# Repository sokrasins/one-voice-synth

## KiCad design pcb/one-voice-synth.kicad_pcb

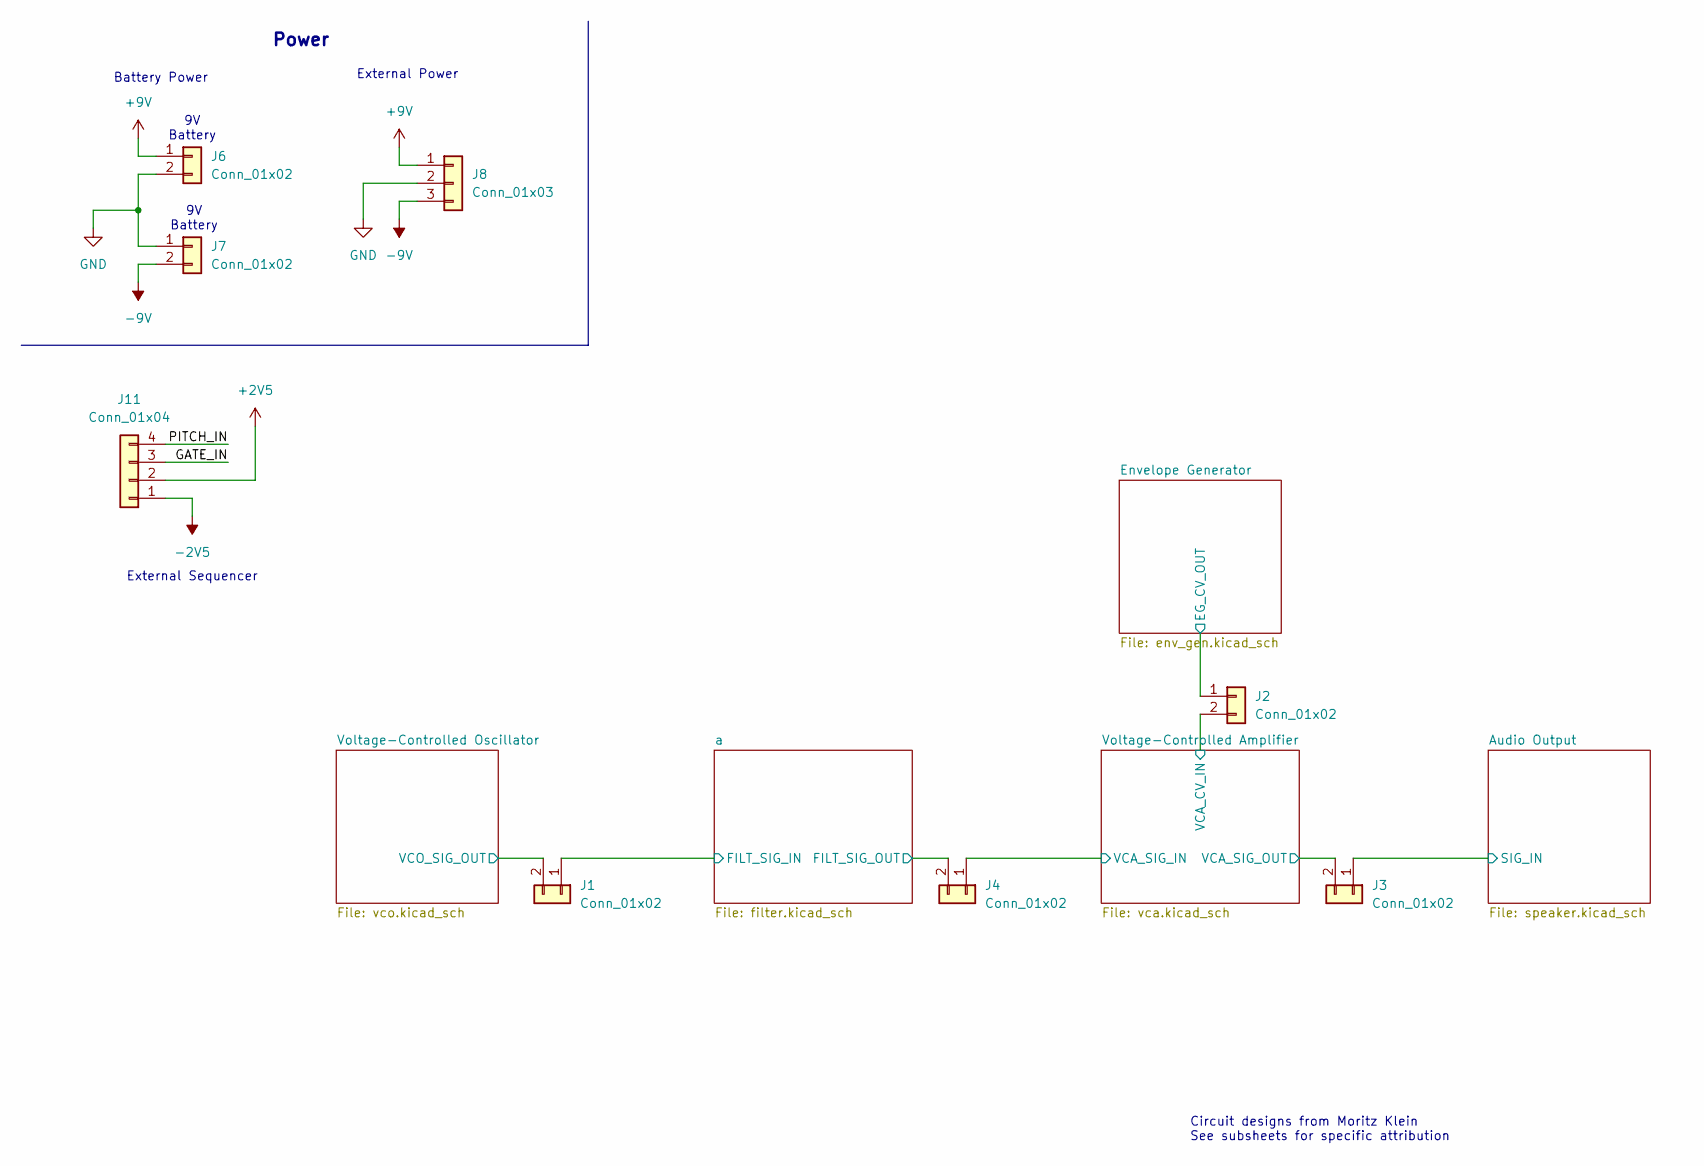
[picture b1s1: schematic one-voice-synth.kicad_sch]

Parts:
J1, J2, J3, J4, J6, J7: Conn_01x02; PinHeader_1x02_P2.54mm_Vertical
J8: Conn_01x03; PinHeader_1x03_P2.54mm_Horizontal
J11: Conn_01x04; PinHeader_1x04_P2.54mm_Vertical

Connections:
+2V5: J11.2; also elsewhere on the board
+9V: J6.1, J8.1; also elsewhere on the board
-2V5: J11.1; also elsewhere on the board
-9V: J7.2, J8.3; also elsewhere on the board
/Audio Output/SIG_IN: J3.1; also elsewhere on the board
/Envelope Generator/EG_CV_OUT: J2.1; also elsewhere on the board
/GATE_IN: J11.3
/PITCH_IN: J11.4
/Voltage-Controlled Amplifier/VCA_CV_IN: J2.2; also elsewhere on the board
/Voltage-Controlled Amplifier/VCA_SIG_IN: J4.1; also elsewhere on the board
/Voltage-Controlled Amplifier/VCA_SIG_OUT: J3.2; also elsewhere on the board
/Voltage-Controlled Oscillator/VCO_SIG_OUT: J1.2; also elsewhere on the board
/a/FILT_SIG_IN: J1.1; also elsewhere on the board
/a/FILT_SIG_OUT: J4.2; also elsewhere on the board
GND: J6.2, J7.1, J8.2; also elsewhere on the board

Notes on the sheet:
External Sequencer
Power
Circuit designs from Moritz Klein See subsheets for specific attribution
External Power
Battery Power
9V Battery

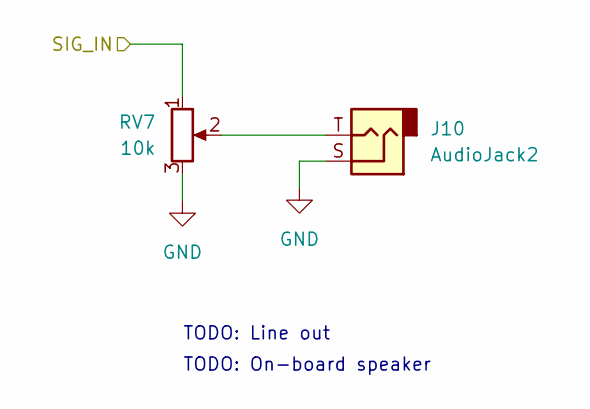
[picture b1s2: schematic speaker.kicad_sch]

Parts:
J10: AudioJack2; Jack_3.5mm_CUI_SJ1-3513N_Horizontal
RV7: 10k; Potentiometer_Bourns_PTV09A-1_Single_Vertical

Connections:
/Audio Output/SIG_IN: RV7.1; also elsewhere on the board
GND: J10.S, RV7.3; also elsewhere on the board
unnamed: J10.T, RV7.2

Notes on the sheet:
TODO: On-board speaker
TODO: Line out

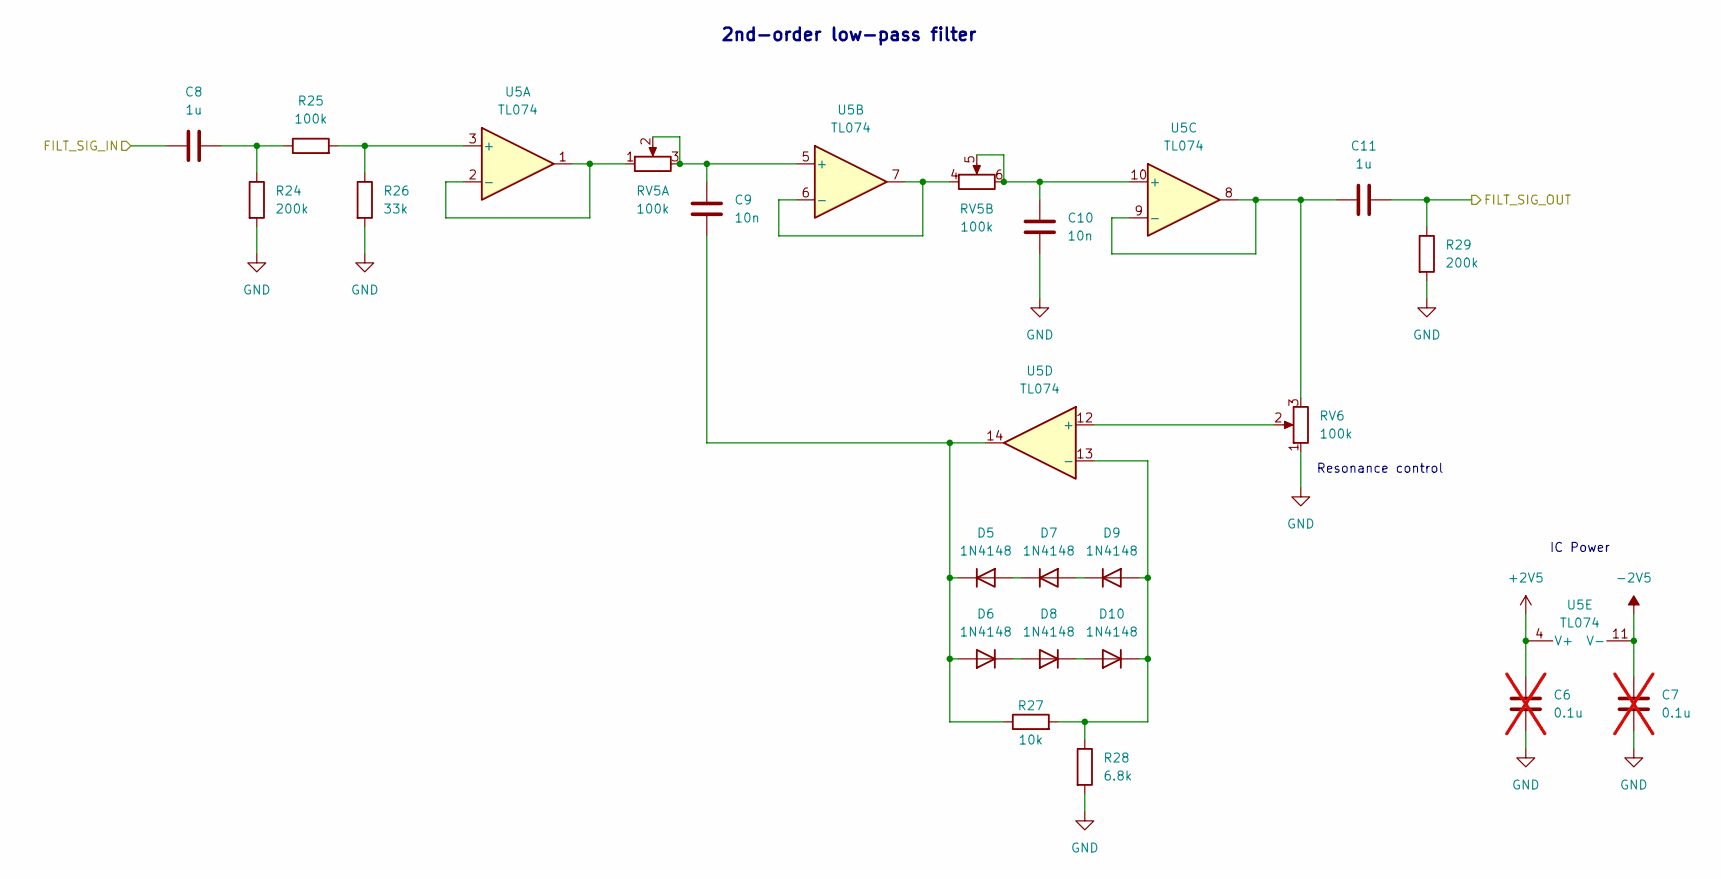
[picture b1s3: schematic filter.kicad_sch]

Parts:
C6, C7: 0.1u; C_Disc_D6.0mm_W2.5mm_P5.00mm; not fitted
C8, C11: 1u; C_Disc_D6.0mm_W2.5mm_P5.00mm
C9, C10: 10n; C_Disc_D6.0mm_W2.5mm_P5.00mm
D5, D6, D7, D8, D9, D10: 1N4148; D_DO-35_SOD27_P7.62mm_Horizontal
R24, R29: 200k; R_Axial_DIN0207_L6.3mm_D2.5mm_P10.16mm_Horizontal
R25: 100k; R_Axial_DIN0207_L6.3mm_D2.5mm_P10.16mm_Horizontal
R26: 33k; R_Axial_DIN0207_L6.3mm_D2.5mm_P10.16mm_Horizontal
R27: 10k; R_Axial_DIN0207_L6.3mm_D2.5mm_P10.16mm_Horizontal
R28: 6.8k; R_Axial_DIN0207_L6.3mm_D2.5mm_P10.16mm_Horizontal
RV5: 100k; Potentiometer_Bourns_PTV112-4_Dual_Vertical
RV6: 100k; Potentiometer_Bourns_PTV09A-1_Single_Vertical
U5: TL074; DIP-14_W7.62mm

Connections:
+2V5: C6.1, U5.4 (V+); also elsewhere on the board
-2V5: C7.1, U5.11 (V-); also elsewhere on the board
/a/FILT_SIG_IN: C8.1; also elsewhere on the board
/a/FILT_SIG_OUT: C11.2, R29.1; also elsewhere on the board
GND: C6.2, C7.2, C10.2, R24.2, R26.2, R28.2, R29.2, RV6.1; also elsewhere on the board
unnamed: C8.2, R24.1, R25.1
unnamed: D5.2 (A), D7.1 (K)
unnamed: C9.2, D5.1 (K), D6.2 (A), R27.1, U5.14
unnamed: D6.1 (K), D8.2 (A)
unnamed: D7.2 (A), D9.1 (K)
unnamed: D8.1 (K), D10.2 (A)
unnamed: D9.2 (A), D10.1 (K), R27.2, R28.1, U5.13 (-)
unnamed: R25.2, R26.1, U5.3 (+)
unnamed: RV5.1, U5.1, U5.2 (-)
unnamed: C9.1, RV5.2, RV5.3, U5.5 (+)
unnamed: RV5.4, U5.6 (-), U5.7
unnamed: C10.1, RV5.5, RV5.6, U5.10 (+)
unnamed: C11.1, RV6.3, U5.8, U5.9 (-)
unnamed: RV6.2, U5.12 (+)

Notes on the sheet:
IC Power
Resonance control
2nd-order low-pass filter

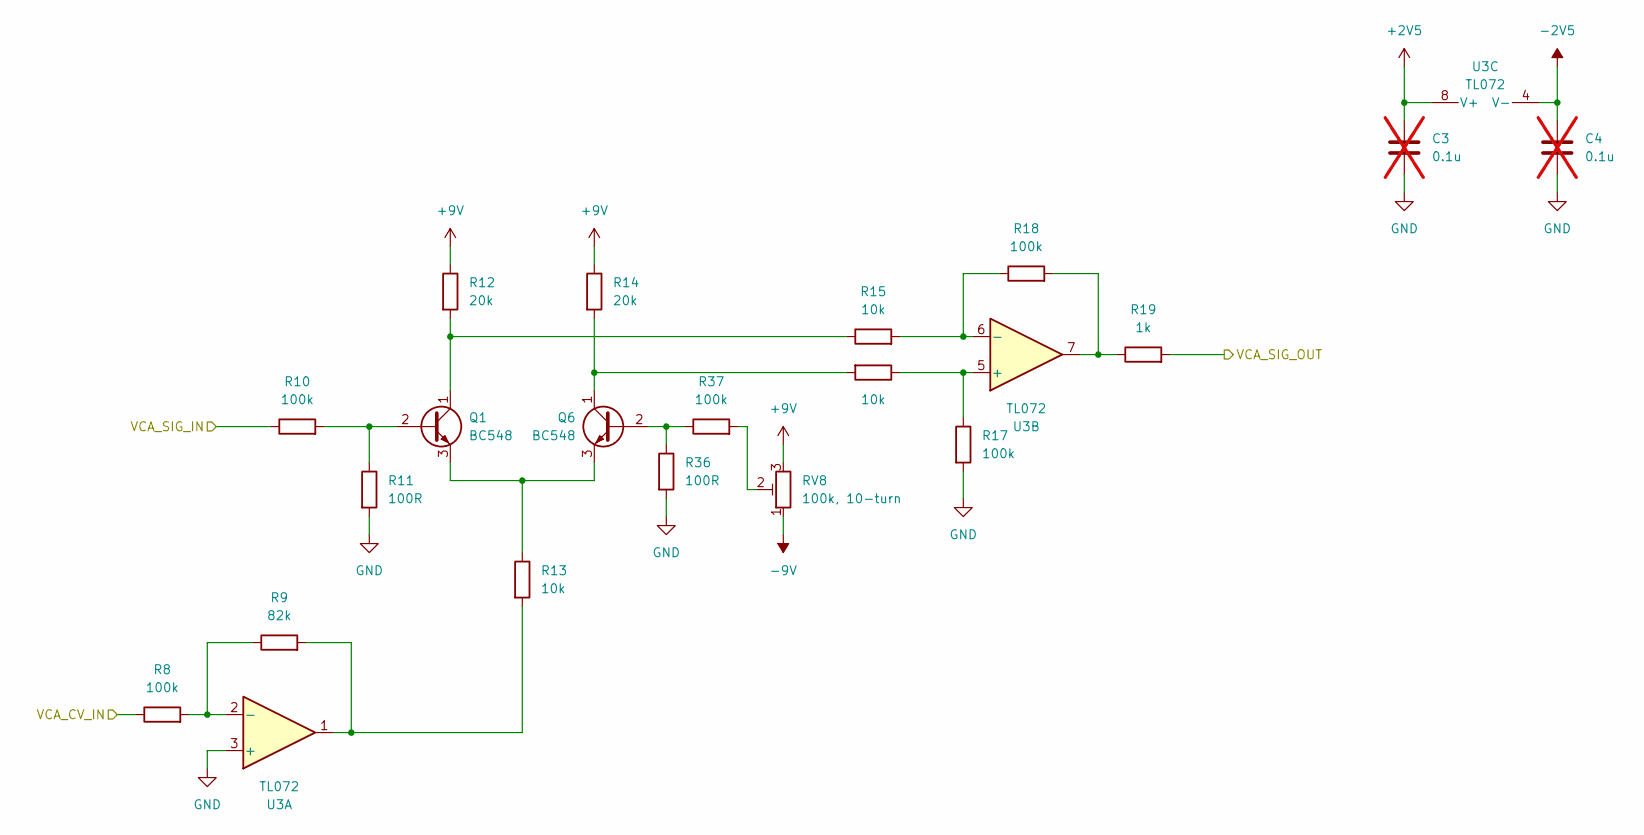
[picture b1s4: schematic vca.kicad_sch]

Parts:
C3, C4: 0.1u; C_Disc_D6.0mm_W2.5mm_P5.00mm; not fitted
Q1, Q6: BC548; TO-92_Inline
R8, R10, R17, R18, R37: 100k; R_Axial_DIN0207_L6.3mm_D2.5mm_P10.16mm_Horizontal
R9: 82k; R_Axial_DIN0207_L6.3mm_D2.5mm_P10.16mm_Horizontal
R11, R36: 100R; R_Axial_DIN0207_L6.3mm_D2.5mm_P10.16mm_Horizontal
R12, R14: 20k; R_Axial_DIN0207_L6.3mm_D2.5mm_P10.16mm_Horizontal
R13, R15, R16: 10k; R_Axial_DIN0207_L6.3mm_D2.5mm_P10.16mm_Horizontal
R19: 1k; R_Axial_DIN0207_L6.3mm_D2.5mm_P10.16mm_Horizontal
RV8: 100k, 10-turn; Potentiometer_Bourns_3296W_Vertical
U3: TL072; DIP-8_W7.62mm

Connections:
+2V5: C3.1, U3.8 (V+); also elsewhere on the board
+9V: R12.1, R14.1, RV8.3; also elsewhere on the board
-2V5: C4.1, U3.4 (V-); also elsewhere on the board
-9V: RV8.1; also elsewhere on the board
/Voltage-Controlled Amplifier/VCA_CV_IN: R8.1; also elsewhere on the board
/Voltage-Controlled Amplifier/VCA_SIG_IN: R10.1; also elsewhere on the board
/Voltage-Controlled Amplifier/VCA_SIG_OUT: R19.2; also elsewhere on the board
GND: C3.2, C4.2, R11.2, R17.2, R36.2, U3.3 (+); also elsewhere on the board
unnamed: Q1.2 (B), R10.2, R11.1
unnamed: Q1.1 (C), R12.2, R15.1
unnamed: Q1.3 (E), Q6.3 (E), R13.1
unnamed: Q6.2 (B), R36.1, R37.1
unnamed: Q6.1 (C), R14.2, R16.2
unnamed: R9.2, R13.2, U3.1
unnamed: R18.2, R19.1, U3.7
unnamed: R37.2, RV8.2
unnamed: R8.2, R9.1, U3.2 (-)
unnamed: R16.1, R17.1, U3.5 (+)
unnamed: R15.2, R18.1, U3.6 (-)

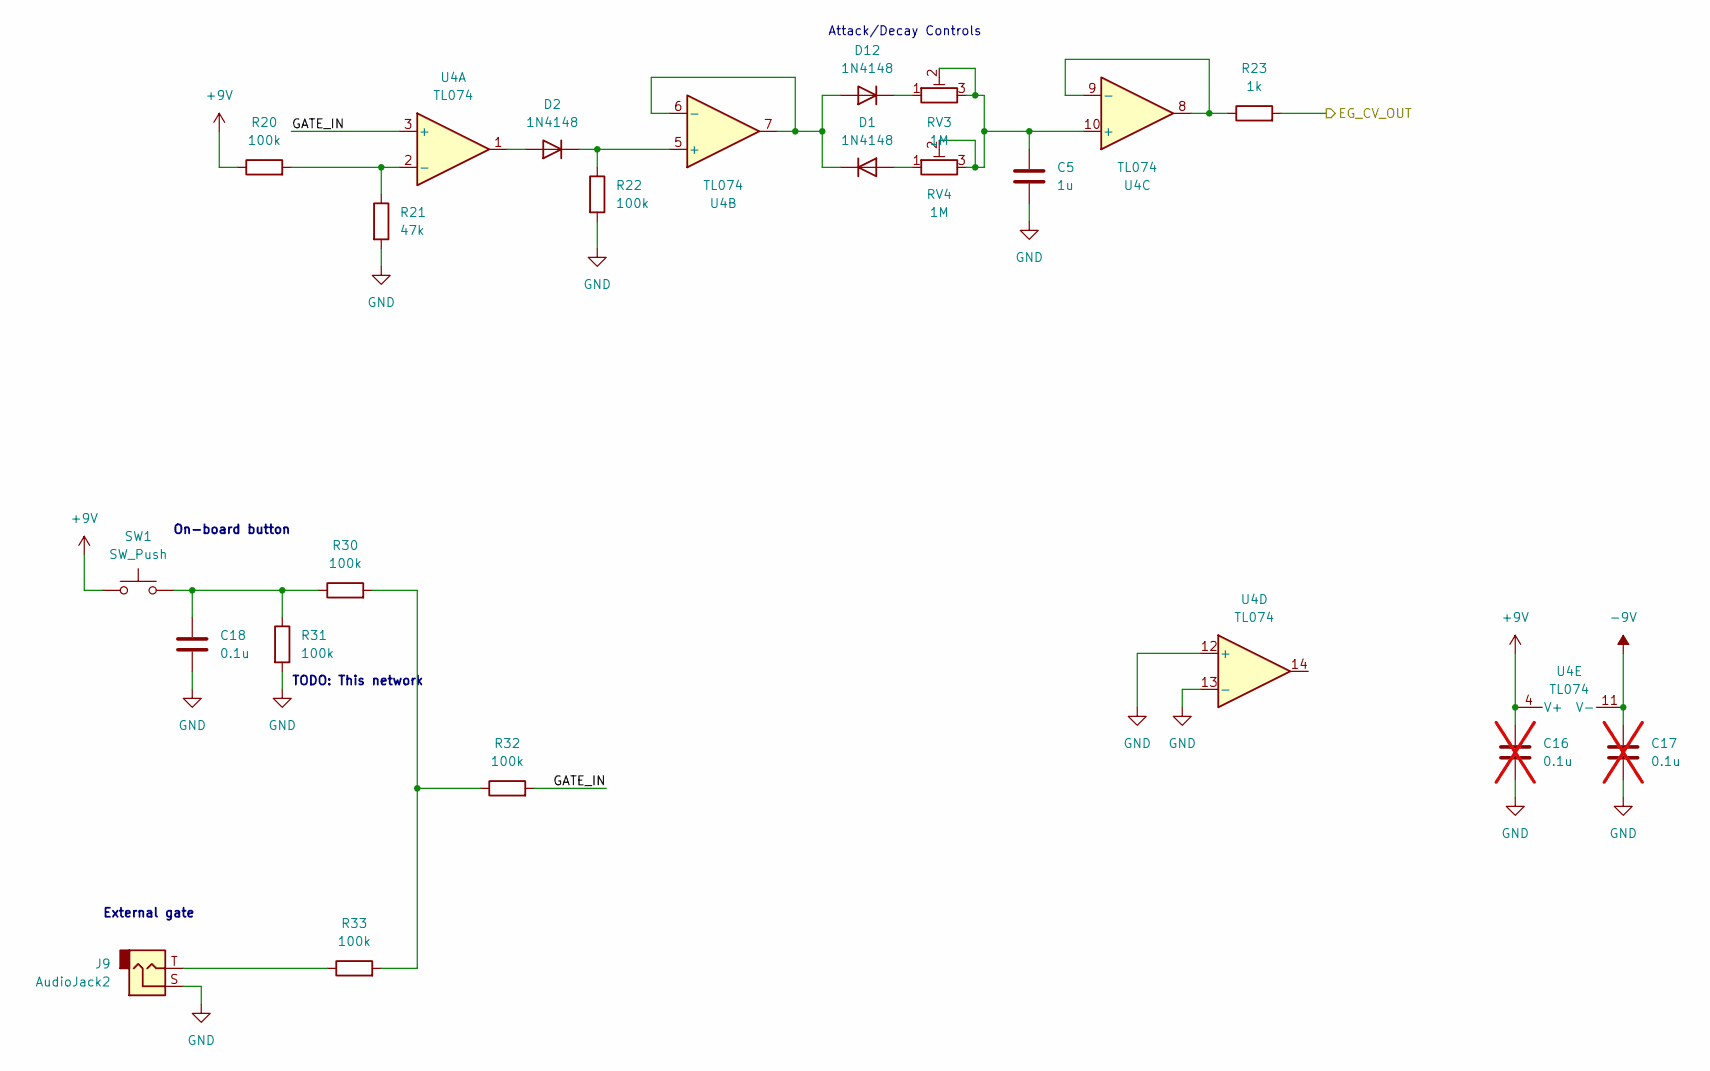
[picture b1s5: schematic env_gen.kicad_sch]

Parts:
C5: 1u; C_Disc_D6.0mm_W2.5mm_P5.00mm
C16, C17: 0.1u; C_Disc_D6.0mm_W2.5mm_P5.00mm; not fitted
C18: 0.1u; C_Disc_D6.0mm_W2.5mm_P5.00mm
D1, D2, D12: 1N4148; D_DO-35_SOD27_P7.62mm_Horizontal
J9: AudioJack2; Jack_3.5mm_CUI_SJ1-3513N_Horizontal
R20, R22, R30, R31, R32, R33: 100k; R_Axial_DIN0207_L6.3mm_D2.5mm_P10.16mm_Horizontal
R21: 47k; R_Axial_DIN0207_L6.3mm_D2.5mm_P10.16mm_Horizontal
R23: 1k; R_Axial_DIN0207_L6.3mm_D2.5mm_P10.16mm_Horizontal
RV3, RV4: 1M; Potentiometer_Bourns_PTV09A-1_Single_Vertical
SW1: SW_Push; SW_Cherry_MX_1.00u_PCB
U4: TL074; DIP-14_W7.62mm

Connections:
+9V: C16.1, R20.1, SW1.1, U4.4 (V+); also elsewhere on the board
-9V: C17.1, U4.11 (V-); also elsewhere on the board
/Envelope Generator/EG_CV_OUT: R23.2; also elsewhere on the board
/Envelope Generator/GATE_IN: R32.2, U4.3 (+)
GND: C5.2, C16.2, C17.2, C18.2, J9.S, R21.2, R22.2, R31.2, U4.12 (+), U4.13 (-); also elsewhere on the board
unnamed: C18.1, R30.1, R31.1, SW1.2
unnamed: D1.2 (A), RV4.1
unnamed: D1.1 (K), D12.2 (A), U4.6 (-), U4.7
unnamed: D2.2 (A), U4.1
unnamed: D2.1 (K), R22.1, U4.5 (+)
unnamed: D12.1 (K), RV3.1
unnamed: J9.T, R33.1
unnamed: R30.2, R32.1, R33.2
unnamed: R20.2, R21.1, U4.2 (-)
unnamed: C5.1, RV3.2, RV3.3, RV4.2, RV4.3, U4.10 (+)
unnamed: R23.1, U4.8, U4.9 (-)

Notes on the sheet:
External gate
TODO: This network
Attack/Decay Controls
On-board button

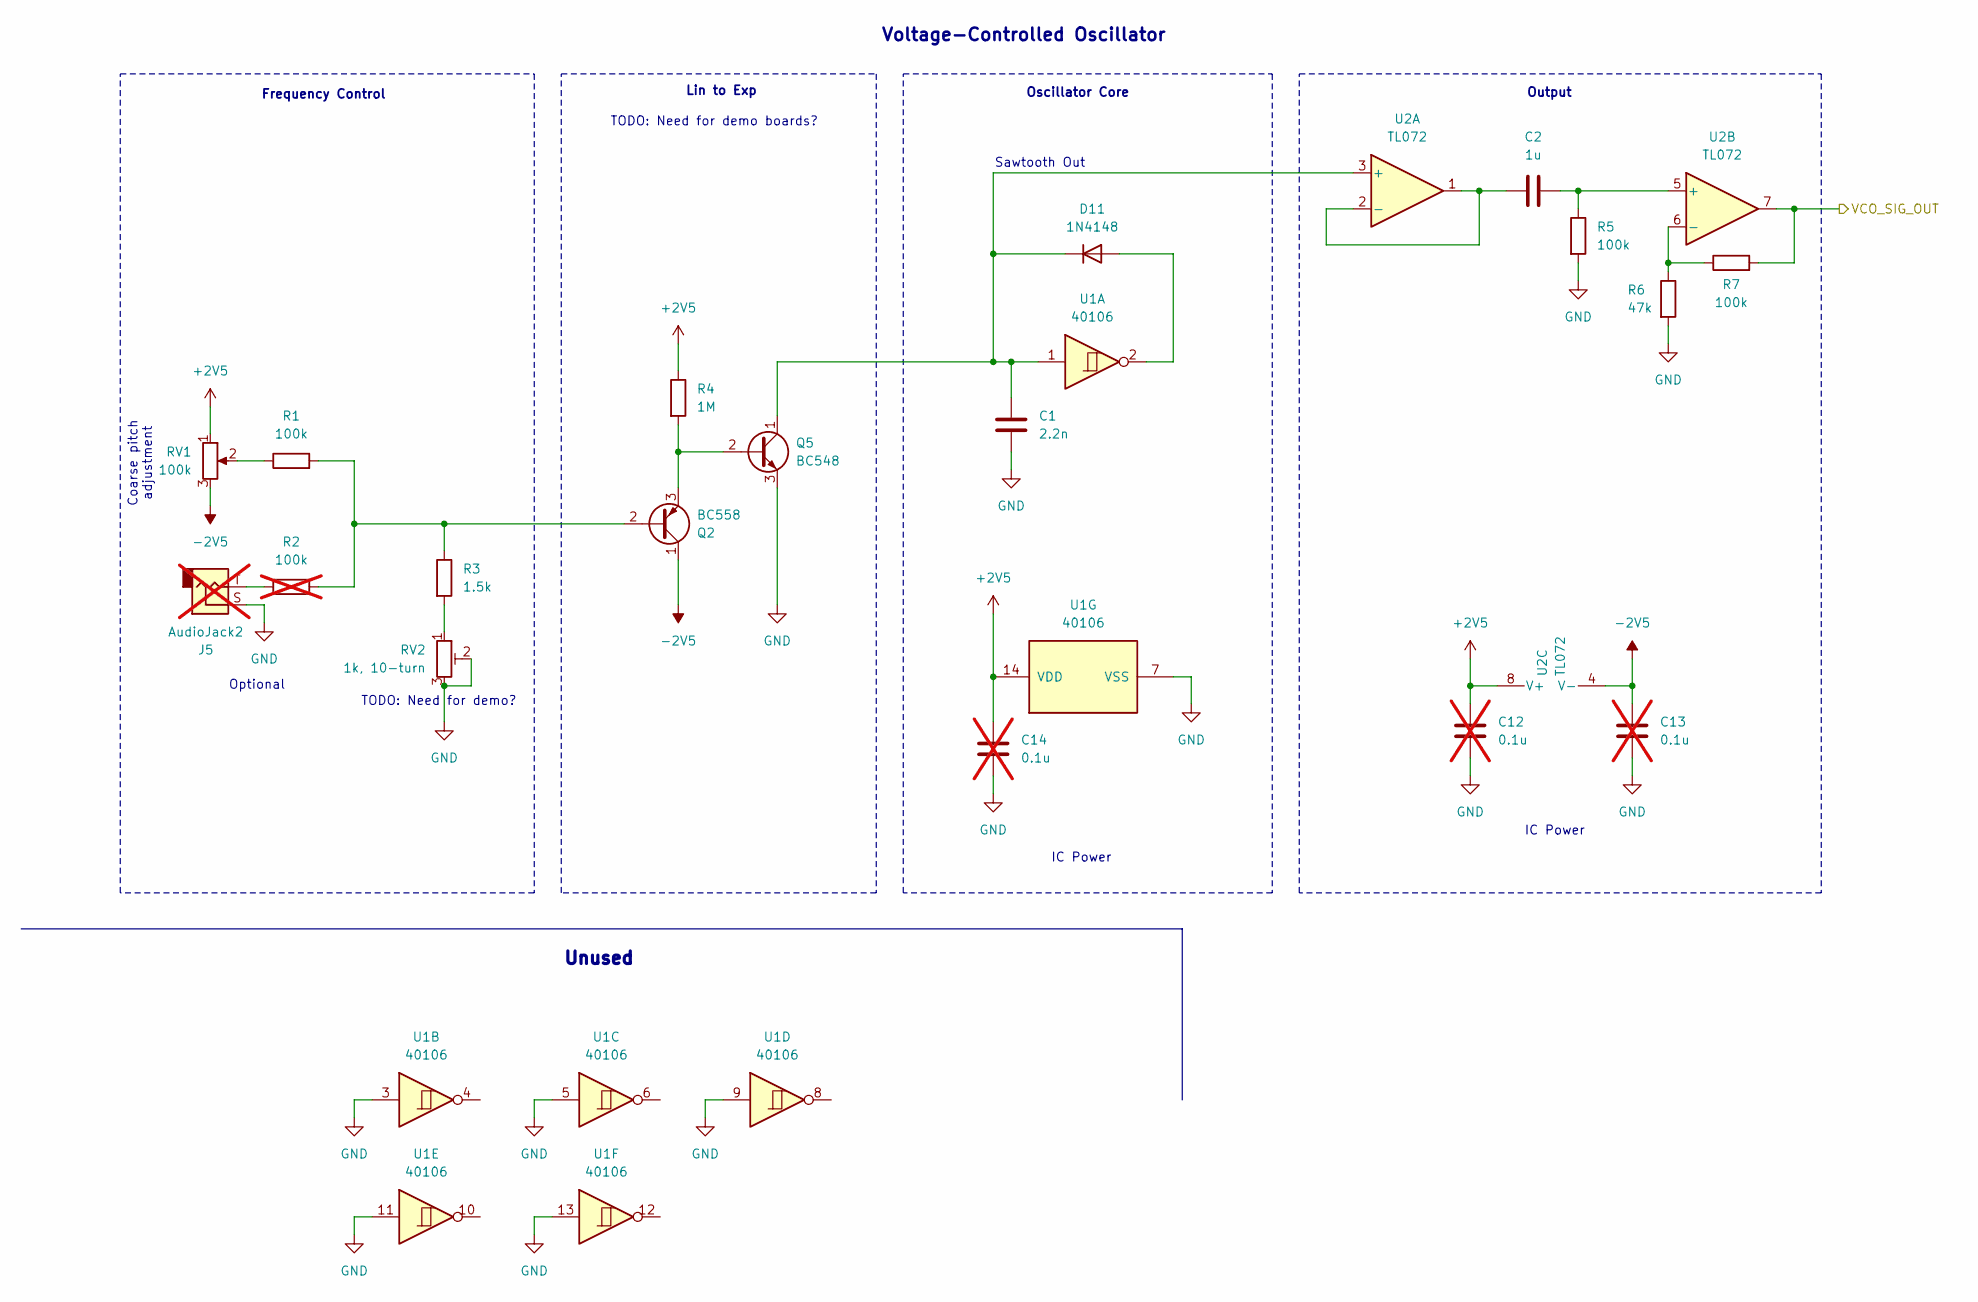
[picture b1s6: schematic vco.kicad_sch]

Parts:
C1: 2.2n; C_Disc_D6.0mm_W2.5mm_P5.00mm
C2: 1u; C_Disc_D6.0mm_W2.5mm_P5.00mm
C12, C13, C14: 0.1u; C_Disc_D6.0mm_W2.5mm_P5.00mm; not fitted
D11: 1N4148; D_DO-35_SOD27_P7.62mm_Horizontal
J5: AudioJack2; Jack_3.5mm_CUI_SJ1-3513N_Horizontal; not fitted
Q2: BC558; TO-92_Inline
Q5: BC548; TO-92_Inline
R1, R5, R7: 100k; R_Axial_DIN0207_L6.3mm_D2.5mm_P10.16mm_Horizontal
R2: 100k; R_Axial_DIN0207_L6.3mm_D2.5mm_P10.16mm_Horizontal; not fitted
R3: 1.5k; R_Axial_DIN0207_L6.3mm_D2.5mm_P10.16mm_Horizontal
R4: 1M; R_Axial_DIN0207_L6.3mm_D2.5mm_P10.16mm_Horizontal
R6: 47k; R_Axial_DIN0207_L6.3mm_D2.5mm_P10.16mm_Horizontal
RV1: 100k; Potentiometer_Bourns_PTV09A-1_Single_Vertical
RV2: 1k, 10-turn; Potentiometer_Bourns_3296W_Vertical
U1: 40106; DIP-14_W7.62mm
U2: TL072; DIP-8_W7.62mm

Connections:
+2V5: C12.1, C14.1, R4.1, RV1.1, U1.14 (VDD), U2.8 (V+); also elsewhere on the board
-2V5: C13.1, Q2.1 (C), RV1.3, U2.4 (V-); also elsewhere on the board
/Voltage-Controlled Oscillator/VCO_SIG_OUT: R7.2, U2.7; also elsewhere on the board
GND: C1.2, C12.2, C13.2, C14.2, J5.S, Q5.3 (E), R5.2, R6.2, RV2.2, RV2.3, U1.3, U1.5, U1.7 (VSS), U1.9, U1.11, U1.13; also elsewhere on the board
unnamed: D11.2 (A), U1.2
unnamed: C1.1, D11.1 (K), Q5.1 (C), U1.1, U2.3 (+)
unnamed: J5.T, R2.1
unnamed: Q2.2 (B), R1.2, R2.2, R3.1
unnamed: Q2.3 (E), Q5.2 (B), R4.2
unnamed: R1.1, RV1.2
unnamed: R3.2, RV2.1
unnamed: C2.1, U2.1, U2.2 (-)
unnamed: C2.2, R5.1, U2.5 (+)
unnamed: R6.1, R7.1, U2.6 (-)

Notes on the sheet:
Unused
Coarse pitch adjustment
Optional
TODO: Need for demo boards?
IC Power
Oscillator Core
Lin to Exp
Frequency Control
Sawtooth Out
TODO: Need for demo?
Voltage-Controlled Oscillator
Output

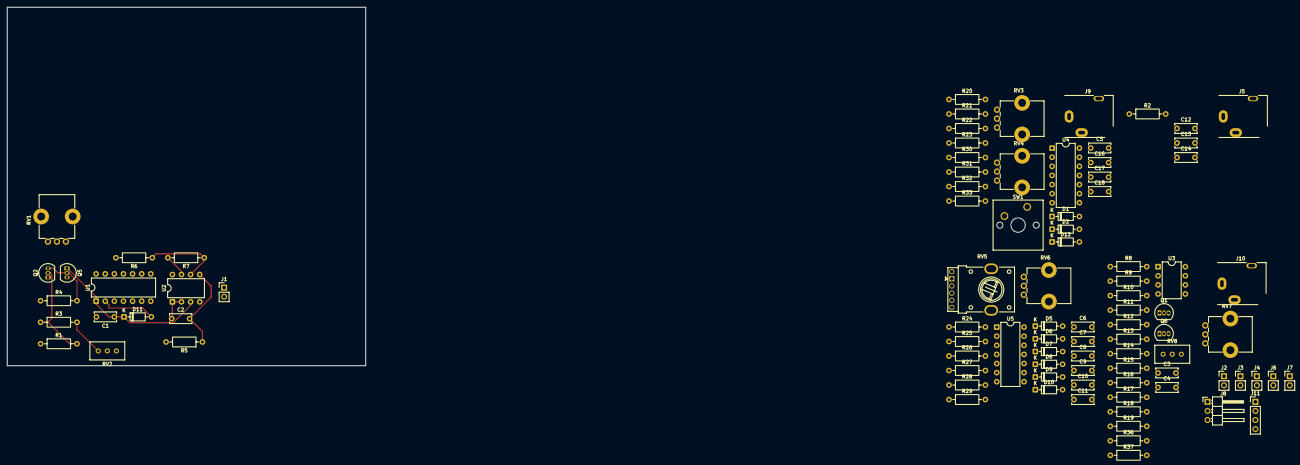
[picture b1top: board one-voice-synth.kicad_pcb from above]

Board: 2 copper layers, 100.0 x 100.0 mm, 91 parts (0 on the bottom side), 61 nets.

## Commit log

2025-09-20 Add schematic
2025-09-24 update vca
2025-09-25 Update rails, start to clean
2025-09-25 Didn't save
2025-09-25 Fix some labeling and DNP statues
